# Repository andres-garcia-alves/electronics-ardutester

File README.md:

# ArduTester v1.08k OLED

Electronic project for use an Arduino Nano as an electronics components identifier.  
Schematics diagram + PCB diagram (KiCAD 9) and case 3D model (Blender) are also provided.  

This project is a **work-in-progress**.

Based on the well-known **TransistorTester** work of [Karl-Heinz Kübbeler](https://github.com/kubi48/).

Useful links:  
- [TransistorTester oficial GitHub](https://github.com/kubi48/TransistorTester-source)  
- [Mikrocontroller.net](https://www.mikrocontroller.net/articles/AVR_Transistortester)  
- [Mikrocontroller.net GitHub](https://github.com/Mikrocontroller-net/transistortester/)  

Aditional resources:
- [Electgpl@YouTube.com: Video tutorial: ArduTester + OLED display](https://www.youtube.com/watch?v=M8jgcR9IcJU) [spanish]
- [ElProfeGarcia@YouTube.com: Video tutorial: ArduTester component tester](https://www.youtube.com/watch?v=7o1T-6169ZE) [spanish]
- [Electronoobs@YouTube.com: Video tutorial: component test with Arduino + TFT display](https://www.youtube.com/watch?v=lsy2g0oz0Dk) [spanish]
- [Electronoobs.com blog](https://electronoobs.com/eng_arduino_tut191.php) [spanish]
- [BawejaAkshay@Instructables.com: ArduTester version #1](https://www.instructables.com/Component-Tester-Test-Almost-Anything-/)
- [BawejaAkshay@Instructables.com: ArduTester version #2](https://www.instructables.com/Component-Tester-in-a-Keychain/)
- [Lithium-Ion@Hackster.io blog](https://www.hackster.io/LithiumION/minimal-component-tester-using-arduino-b7b960)
- [RiverTrue@DFRobot.com blog](https://community.dfrobot.com/makelog-312328.html)
- [Plouc68000@ProjectHub.arduino.cc blog](https://projecthub.arduino.cc/plouc68000/ardutester-v113-the-arduino-uno-transistor-tester-2deffc)
- [ChristianIhle@GitHub.com blog](https://github.com/blurpy/transistor-tester)

&nbsp;

This project comes in two versions: `standard` (current) and `extended` (planned). See features bellow.

Features:
- One-key-operation.
- Three test pins for universal use.
- Automated detection of pin assignment, this means the device-under-test can be connected to the tester in any order.

Supported components:
- `Diodes`, `LEDs` and `Zeners`.
  - Diodes will also be displayed with their correctly aligned symbol, pin number, voltage drop, the parasitic capacitance and reverse current will also be measured.
- `Transistors` NPN/PNP BJT, JFET, N-channel/P-channel MOSFET.
  - Measurement of hFE and base-emitter-voltage for bipolar junction transistors, also for Darlingtons.
  - Automated detection of protection diodes in bipolar junction transistors and MOSFETs.
  - Bipolar junction transistors are detected as a transistor with a parasitic transistor (NPNp = NPN + parasitic PNP).
- `Resistors` will be measured with a resolution down to 0.1 ohm.  
  The measurement range is up to 50 Mohm (Megaohm).  
  Resistors below 10 ohm will be measured with the ESR approach and a resolution of 0.01 ohm.
- `Capacitors` in the range 35pF (picofarad) to 100mF (millifarad) can be measured with a resolution down to 1 pF.
  - Measurement of ESR (Equivalent Series Resistance) of capacitors greater than 20 nF is built in. 
  - Vloss of capacitors greater 5 nF is examined. With this it is possible to estimate its Q-factor.
- Resistors and capacitors will be displayed with their respective symbol, pin number and value.
- `Inductances` of 0.01 mH to 20 H can be detected and measured.
- Small `Thyristors` and `TRIACs`.

Notes:
- Be sure to **discharge capacitors** before measure it. Existing voltage can damage your Arduino.

&nbsp;

### List of Materials

The `standard` version uses the following electronic components:
- 1 x Arduino Nano v3
- 1 x OLED display 0.96" 128x64 I2C
- 3 x 680 ohm resistor
- 3 x 470k ohm resistor
- 1 x Push switch button
- 1 x 10k ohm resistor
- 1 x Socket connector 5-pins
- 1 x Bornier connector 2-pins / JST connector 2-pins
- 1 x Bornier connector 3-pins / JST connector 3-pins
- 1 x Bornier connector 4-pins / JST connector 4-pins
- Wires

&nbsp;

### Screenshots

| Breadboard                                           | Assembly                                             |
|------------------------------------------------------|------------------------------------------------------|
|             |            |

| Assembly                                             | Assembly                                             |
|------------------------------------------------------|------------------------------------------------------|
|            |            |

| Schematics Diagram                                   | PCB Diagram                                          |
|------------------------------------------------------|------------------------------------------------------|
|     |            |

| PCB Render 3D                                        | PCB Render 3D                                        |
|------------------------------------------------------|------------------------------------------------------|
|    |   |

| Case 3D Model                                        | Project Final                                        |
|------------------------------------------------------|------------------------------------------------------|
|          |       |

| Project Final                                        | Project Final                                        |
|------------------------------------------------------|------------------------------------------------------|
|       |       |

See 'Resources' sub-folder for more pictures & videos of the project.

&nbsp;

### Version History

v1.0 (2026.01.04) - Initial release.  
v1.1 (2026.01.05) - Added schematics and PCB diagrams.  
v1.2 (2026.01.05) - Added 3D case model.  
v1.3 (2026.01.06) - Firmware and PCB fixes.  
v1.4 (2026.01.06) - 3D case model fixes.  
v1.4 (2026.01.06) - Minor case 3D model fixes.  
v1.5 (2026.01.09) - Minor fixes on PCB.  
v1.6 (2026.01.14) - Minor fixes on PCB.  
v1.7 (2026.01.16) - Re-design of PCB and 3D case model.  
v1.8 (2026.02.03) - Minor cases 3D model fixes.  
v1.9 (2026.02.04) - Added gadget images & video.  

&nbsp;

This source code is licensed under GPL v3.0  
Please send me your feedback about this project: andres.garcia.alves@gmail.com

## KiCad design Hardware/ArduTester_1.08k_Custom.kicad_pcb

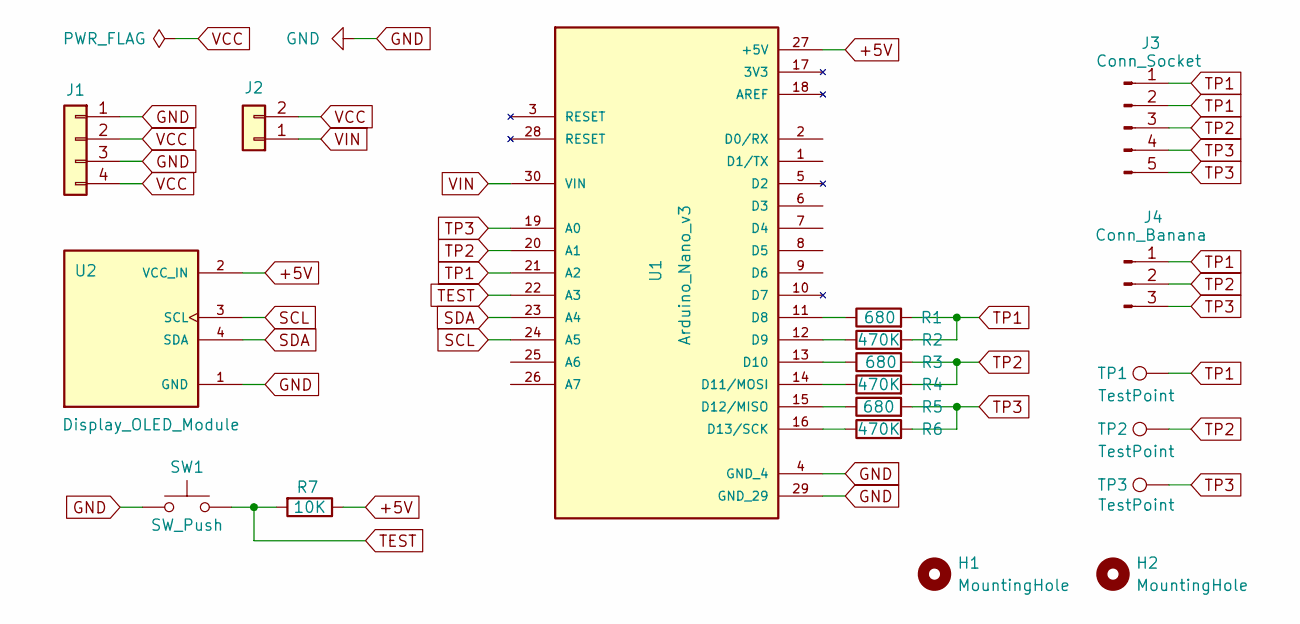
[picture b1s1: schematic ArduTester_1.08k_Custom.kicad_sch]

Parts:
H1, H2: MountingHole; MountingHole_2.2mm_M2
J1: POWER; JST_EH_B4B-EH-A_1x04_P2.50mm_Vertical
J2: SW_BTN; JST_EH_B2B-EH-A_1x02_P2.50mm_Vertical
J3: Conn_Socket; PinSocket_1x05_P2.54mm_Vertical
J4: Conn_Banana; JST_EH_B3B-EH-A_1x03_P2.50mm_Vertical
R1, R3, R5: 680; R_Axial_DIN0204_L3.6mm_D1.6mm_P7.62mm_Horizontal
R2, R4, R6: 470K; R_Axial_DIN0204_L3.6mm_D1.6mm_P7.62mm_Horizontal
R7: 10K; R_Axial_DIN0204_L3.6mm_D1.6mm_P7.62mm_Horizontal
SW1: SW_Push; SW_PUSH_6mm_H9.5mm
TP1, TP2, TP3: TestPoint; TestPoint_Bridge_Pitch2.54mm_Drill0.7mm
U1: Arduino_Nano_v3
U2: Display_OLED_Module; Display_OLED_Module_DM_OLED096_636

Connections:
+5V: R7.1, U1.27 (+5V), U2.2 (VCC_IN)
GND: J1.1, J1.3, SW1.1, U1.4 (GND_4), U1.29 (GND_29), U2.1 (GND)
unnamed: R1.1, U1.11 (D8)
unnamed: R2.1, U1.12 (D9)
unnamed: R3.1, U1.13 (D10)
unnamed: R4.1, U1.14 (D11/MOSI)
unnamed: R5.1, U1.15 (D12/MISO)
unnamed: R6.1, U1.16 (D13/SCK)
SCL: U1.24 (A5), U2.3 (SCL)
SDA: U1.23 (A4), U2.4 (SDA)
TEST: R7.2, SW1.2, U1.22 (A3)
TP1: J3.1, J3.2, J4.1, R1.2, R2.2, TP1.1, U1.21 (A2)
TP2: J3.3, J4.2, R3.2, R4.2, TP2.1, U1.20 (A1)
TP3: J3.4, J3.5, J4.3, R5.2, R6.2, TP3.1, U1.19 (A0)
VCC: J1.2, J1.4, J2.2
VIN: J2.1, U1.30 (VIN)

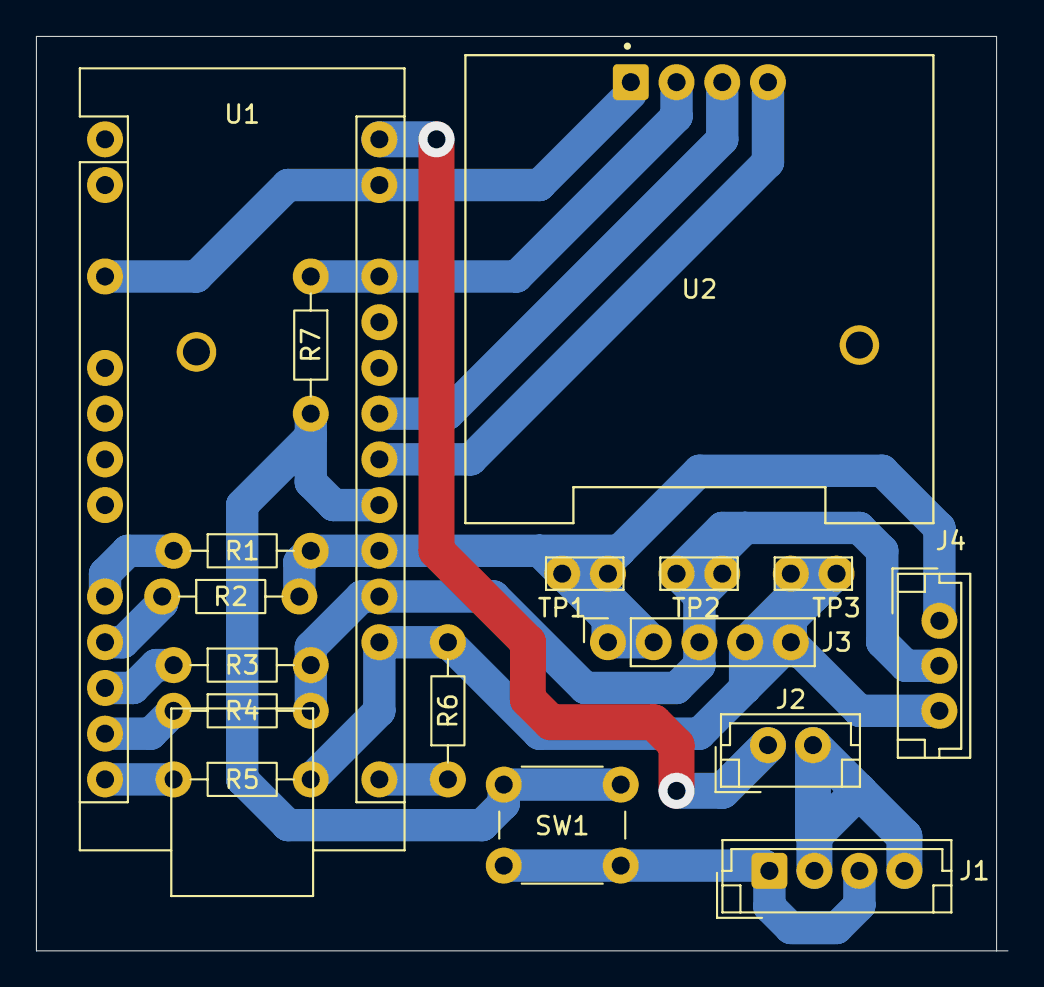
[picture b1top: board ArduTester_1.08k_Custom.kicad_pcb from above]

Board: 2 copper layers, 54.0 x 50.8 mm, 19 parts (0 on the bottom side), 16 nets.
